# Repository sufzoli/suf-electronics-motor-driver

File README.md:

# suf-electronics-motor-driver
Spindle motor driver for my Chinese CNC router

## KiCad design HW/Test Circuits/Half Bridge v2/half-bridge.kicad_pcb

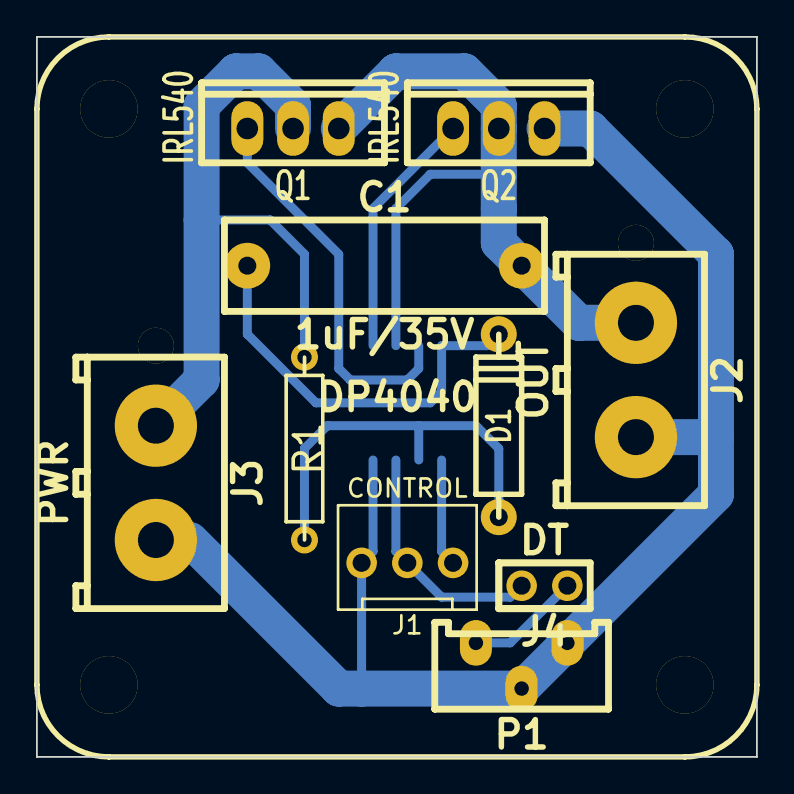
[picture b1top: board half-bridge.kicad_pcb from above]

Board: 2 copper layers, 40.0 x 40.0 mm, 12 parts (1 on the bottom side), 10 nets.

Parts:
C1: 1uF/35V; C6_7x2
D1: 1N5819; D4
DP4040: DP4040
J1: CONTROL; CONN_NCW254-03S
J2: OUT; MOLEX_36538_2
J3: PWR; MOLEX_36538_2
J4: DT; HDR-2
P1: 100K; RV_BOU3296Y
Q1, Q2: IRL540; TO-220_V
R1: 1K8; R4
U1: L6384E; SOIC-8

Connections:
GND: J1.3, J2.2, J3.2, P1.1, P1.2, Q2.3, U1.4
unnamed: J1.1, U1.1
unnamed: J1.2, J4.2, U1.3
unnamed: J4.1, P1.3
unnamed: Q1.1, U1.7
unnamed: Q2.1, U1.5
unnamed: C1.1, D1.2, U1.8
unnamed: D1.1, R1.1, U1.2
unnamed: C1.2, J2.1, Q1.3, Q2.2, U1.6
VCC: J3.1, Q1.2, R1.2

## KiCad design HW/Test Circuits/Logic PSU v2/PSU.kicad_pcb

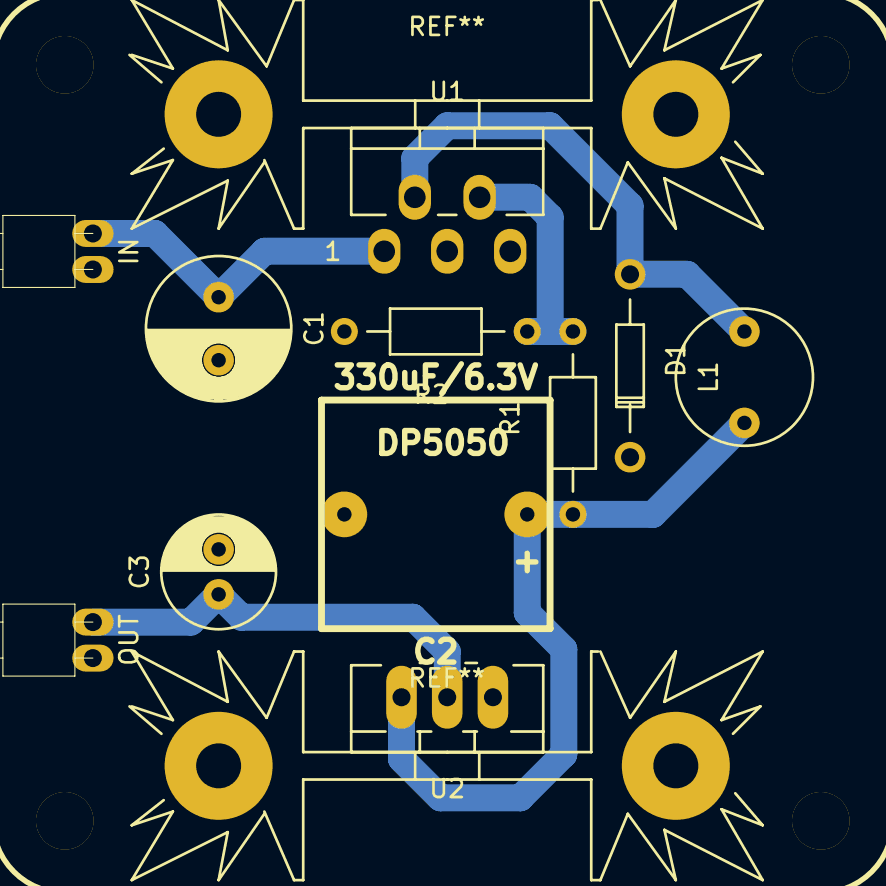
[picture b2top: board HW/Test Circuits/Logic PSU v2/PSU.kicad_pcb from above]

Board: 2 copper layers, 12 parts (0 on the bottom side), 6 nets.

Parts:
C1: 100uF/63V; C_Radial_D8_L11.5_P3.5
C2: 330uF/6.3V; C4P_5X5
C3: 10uF/6,3V; C_Radial_D6.3_L11.2_P2.5
D1: 1N5819; Diode_DO-35_SOD27_Horizontal_RM10
DP5050: DP5050
J1: IN; CONN_NCW254-02R
J2: OUT; CONN_NCW254-02R
L1: 330uH; INDUCTOR_V
R1: 10K; Resistor_Horizontal_RM10mm
R2: 3,3K; Resistor_Horizontal_RM10mm
U1: LM2575; Pentawatt_Neutral_Staggered_Verical_TO220-5-T05D
U2: LD1117V33; TO-220_Neutral123_Vertical_LargePads

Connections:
GND: C1.2, C2.2, C3.2, D1.1, J1.1, J2.1, R2.2, U1.3, U1.5, U2.1
unnamed: C1.1, J1.2, U1.1
unnamed: C2.1, L1.2, R1.1, U2.3
unnamed: C3.1, J2.2, U2.2
unnamed: D1.2, L1.1, U1.2
unnamed: R1.2, R2.1, U1.4

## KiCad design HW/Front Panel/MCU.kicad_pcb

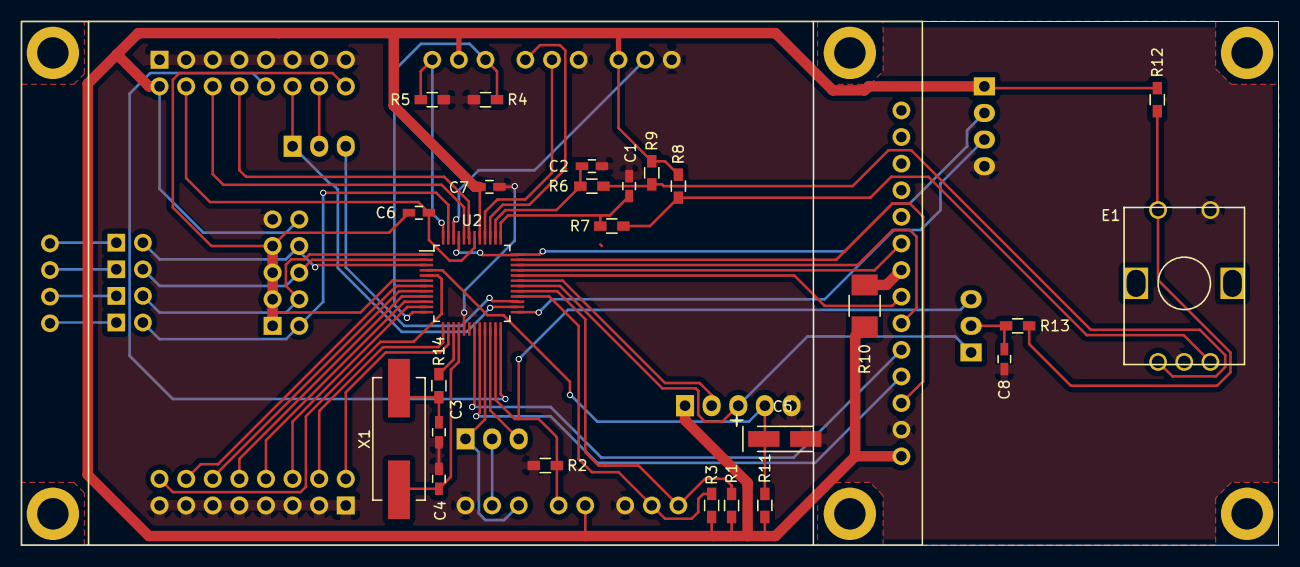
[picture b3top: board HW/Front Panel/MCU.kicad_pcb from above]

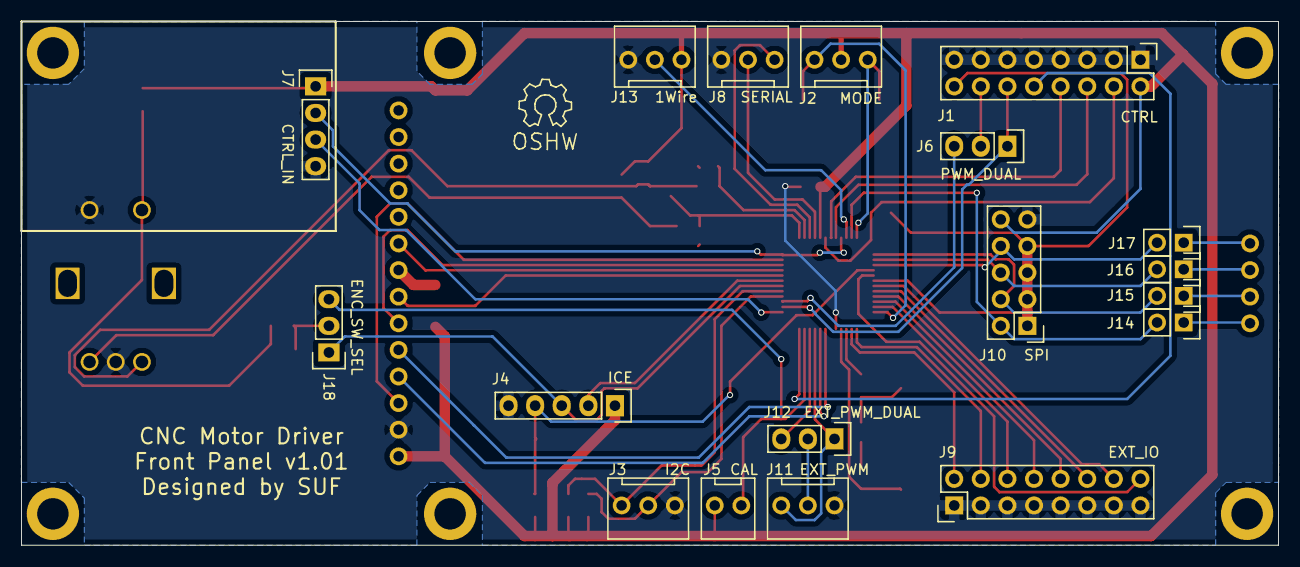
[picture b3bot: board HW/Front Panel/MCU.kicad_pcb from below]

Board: 2 copper layers, 120.0 x 50.0 mm, 46 parts (18 on the bottom side), 58 nets.

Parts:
C1, C2, C8: 10nF; C_0603_HandSoldering
C3, C4: 22pF; C_0603_HandSoldering
C5: 10uF/10V Tantalum; TantalC_SizeA_EIA-3216_HandSoldering
C6, C7: 100nF; C_0603_HandSoldering
E1: EC11P20
J1: CTRL; Pin_Header_Straight_2x08
J2: MODE; CONN_NCW254-03S
J3: I2C; CONN_NCW254-03S
J4: ICE; Pin_Header_Straight_1x05
J5: CAL; CONN_NCW254-02S
J6: PWM_DUAL; Pin_Header_Straight_1x03
J7: CTRL_IN; Pin_Header_Straight_1x04
J8: SERIAL; CONN_NCW254-03S
J9: EXT_IO; Pin_Header_Straight_2x08
J10: SPI; Pin_Header_Straight_2x05
J11: EXT_PWM; CONN_NCW254-03S
J12: EXT_PWM_DUAL; Pin_Header_Straight_1x03
J13: 1Wire; CONN_NCW254-03S
J14, J15, J16, J17: JUMPER; Pin_Header_Straight_1x02
J18: ENC_SW_SEL; Pin_Header_Straight_1x03
MNT_HOLE_3, MNT_HOLE_3#2: Val**; MNT_HOLE_3
R1, R3, R6, R7, R8, R9, R11, R12, R13: 10K; R_0603_HandSoldering
R2, R4, R5: 47K; R_0603_HandSoldering
R10: 3R9; R_1210_HandSoldering
R14: 33; R_0603_HandSoldering
U2: M0516LDN; LQFP-48_7x7mm_Pitch0.5mm
U3: TJCTM24028-SPI
X1: XTAL; Crystal_HC49-SD_SMD

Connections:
1Wire: J13.2, U2.46
ADC_I: J1.8, U2.43
ADC_U: J1.6, U2.44
CAL: J5.2, J18.3, R2.1, U2.23
ENC_A: C2.1, R6.1, U2.38
ENC_B: C1.1, R7.1, U2.37
GND: C1.2, C2.2, C3.1, C4.1, C5.2, C7.2, C8.2, E1.1, E1.5, J1.1, J1.3, J1.5, J1.7, J1.9, J1.11, J1.13, J1.15, J3.3, J4.5, J7.4, J8.3, J9.1, J9.3, J9.5, J9.7, J9.9, J9.11, J9.13, J9.15, J10.9, J11.3, J13.3, R2.2, R4.2, R5.2, U2.17, U3.2
GNDA: C6.2, J1.16, J10.1, J10.3, J10.5, J10.7, U2.6
I2C_SCL: J3.2, R3.2, U2.28
I2C_SDA: J3.1, R1.2, U2.29
MODE_AUTO: J2.3, R4.1, U2.12
MODE_RPM: J2.1, R5.1, U2.48
unnamed: C3.2, R14.1, X1.2
unnamed: C8.1, J18.2, R13.2
unnamed: E1.2, R6.2, R9.2
unnamed: E1.3, R7.2, R8.2
unnamed: E1.4, R12.2, R13.1
unnamed: J1.14, J6.2
unnamed: J11.2, J12.2
unnamed: J14.1, U3.15
unnamed: J15.1, U3.16
unnamed: J16.1, U3.17
unnamed: J17.1, U3.18
unnamed: R10.2, U3.8
PP0: J9.16, U2.5
PP1: J9.14, U2.7
PP2: J9.12, U2.8
PP3: J9.10, U2.9
PP4: J9.8, U2.10
PP5: J9.6, U2.11
PP6: J9.4, U2.13
PP7: J9.2, U2.14
PWM_0: J1.12, J6.1, U2.26
PWM_1: J6.3, U2.27
PWM_2: J11.1, J12.1, U2.21
PWM_3: J12.3, U2.22
RPM_IN: J1.10, U2.24
RXD: J8.1, U2.39
SPINDLE_SPEED: J7.2, U2.36, U2.45
SPINDLE_SWITCH: J7.3, U2.25
SPI_MISO: J10.6, J16.2, U2.2
SPI_MOSI: J10.4, J15.2, U2.1
SPI_SCK: J10.8, J17.2, U2.3
SPI_SS: J10.2, J14.2, U2.47
TFT_CS: U2.35, U3.3
TFT_DC: U2.19, U3.5
TFT_MISO: U2.33, U3.9
TFT_MOSI: U2.34, U3.6
TFT_RST: U2.20, U3.4
TFT_SCK: U2.32, U3.7
TICECLK: J4.3, J18.1, U2.30
TICEDAT: J4.2, U2.31
TICERST: C5.1, J4.4, R11.2, U2.4
TXD: J8.2, U2.40
VCC: C7.1, J1.2, J2.2, J4.1, J5.1, J7.1, J10.10, J13.1, R1.1, R3.1, R8.1, R9.1, R10.1, R11.1, R12.1, U2.41, U3.1
VDD: C6.1, J1.4, U2.42
X1: C4.2, U2.16, X1.1
X2: R14.2, U2.15

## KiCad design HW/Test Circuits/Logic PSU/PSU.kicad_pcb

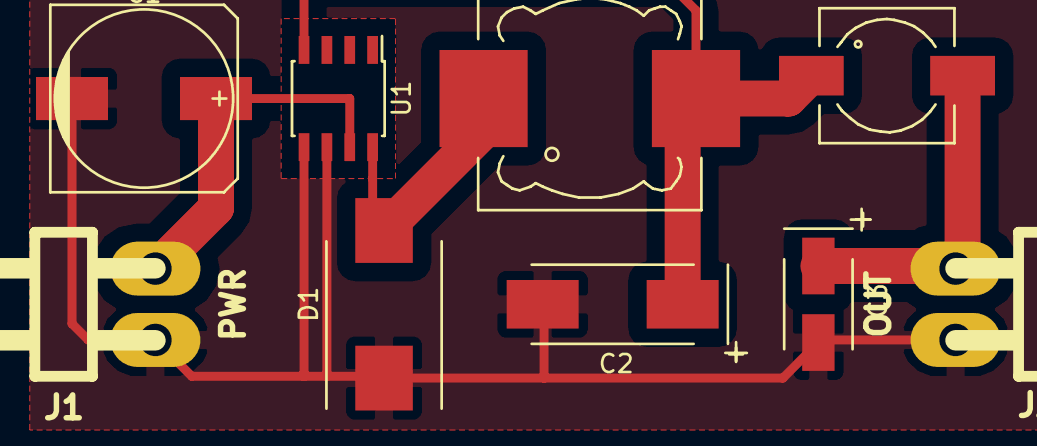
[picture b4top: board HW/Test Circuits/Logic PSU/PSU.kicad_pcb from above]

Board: 2 copper layers, 9 parts (0 on the bottom side), 5 nets.

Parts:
C1: 100uF/63V; c_elec_10x10.5
C2: 220uF/10V Tantalum; TantalC_SizeD_EIA-7343_HandSoldering
C3: 100uF/6.3V Tantalum; TantalC_SizeB_EIA-3528_HandSoldering
D1: SS14; Diode-DO-214AB_Handsoldering
J1: PWR; CONN_NCW396-02R
J2: OUT; CONN_NCW396-02R
L1: 100uH; Choke_SMD_Wuerth-WE-PD-Typ-LS_Handsoldering
L2: 3.3uH; Choke_SMD_Wuerth-WE-PD-Typ-M-Typ-S_Handsoldering
U1: LM2594HVM-3.3; SOIC-8_3.9x4.9mm_Pitch1.27mm

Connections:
GND: C1.2, C2.2, C3.2, D1.1, J1.1, J2.2, U1.5, U1.6
unnamed: C2.1, L1.2, L2.1, U1.4
unnamed: D1.2, L1.1, U1.8
VCC: C3.1, J2.1, L2.2
VDD: C1.1, J1.2, U1.7

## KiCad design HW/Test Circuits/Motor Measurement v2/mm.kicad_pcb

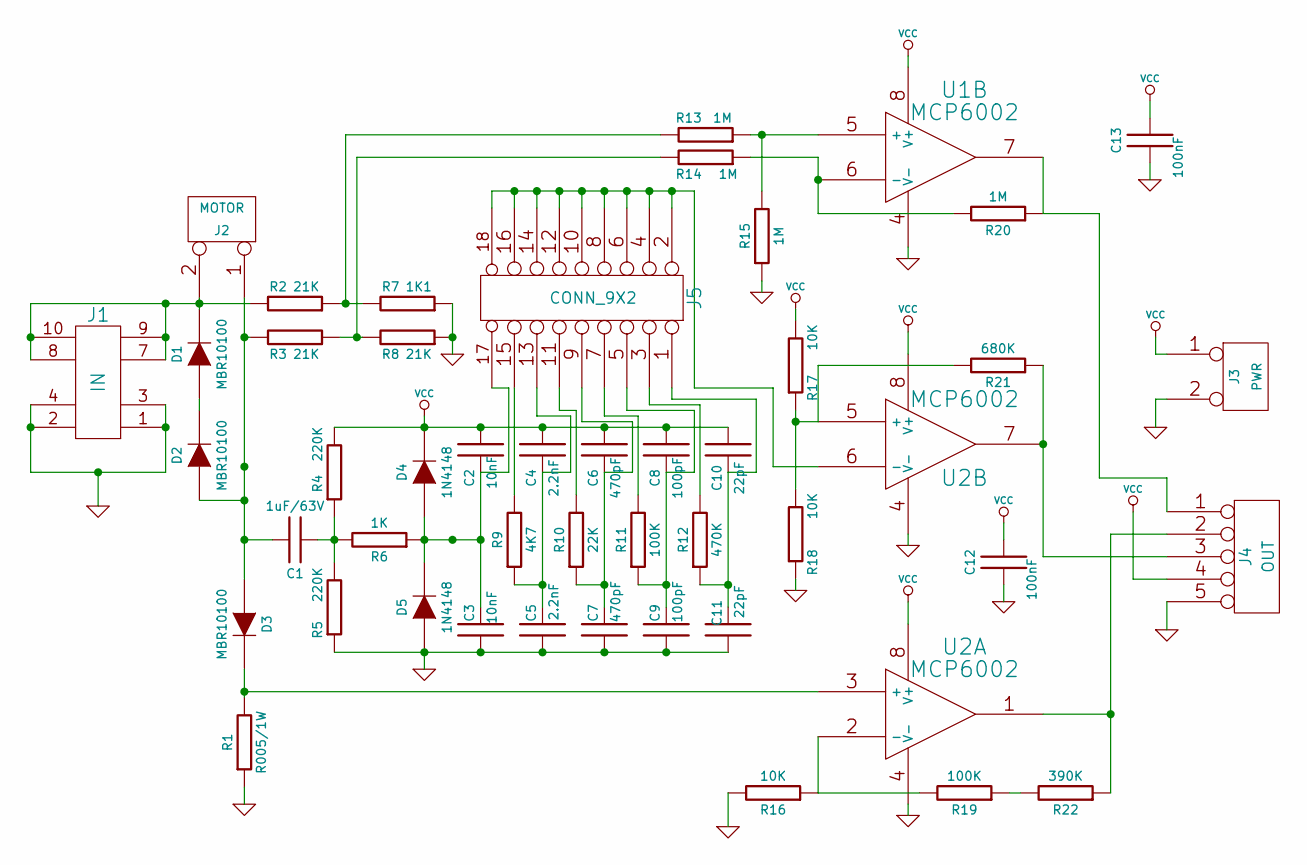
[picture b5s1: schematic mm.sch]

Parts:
C1: 1uF/63V; C2_3x1,75
C2, C3: 10nF; C1
C4, C5: 2.2nF; C1
C6, C7: 470pF; C1
C8, C9: 100pF; C1
C10, C11: 22pF; C1
C12, C13: 100nF; C1
D1, D2, D3: MBR10100; TO220-2
D4, D5: 1N4148; D2
J1: IN; MD-TEST-HDR-F
J2: MOTOR; MOLEX_36538_2
J3: PWR; CONN_NCW254-02S
J4: OUT; CONN_NCW254-05S
J5: CONN_9X2; HDR-9x2
R1: R005/1W; SM2512
R2, R3, R8: 21K; R4
R4, R5: 220K; R4
R6: 1K; R4
R7: 1K1; R4
R9: 4K7; R4
R10: 22K; R4
R11, R19: 100K; R4
R12: 470K; R4
R13, R14, R15, R20: 1M; R4
R16, R17, R18: 10K; R4
R21: 680K; R4
R22: 390K; R4
U1, U2: MCP6002; DIP-8

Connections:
GND: C3.2, C5.2, C7.2, C9.2, C11.2, C12.2, C13.2, D5.1 (A), J1.1, J1.2, J1.3, J1.4, J3.2 (PM), J4.5, R1.2, R5.2, R7.2, R8.2, R15.2, R16.1, R18.2, U1.4 (V-), U2.4 (V-)
unnamed: C1.1, D2.3 (A), D3.3 (A), J2.1, R3.1
unnamed: C1.2, R4.2, R5.1, R6.1
unnamed: C2.2, C3.1, D4.1 (A), D5.2 (K), J5.17, R6.2
unnamed: C4.2, C5.1, J5.13, R9.2
unnamed: C6.2, C7.1, J5.9, R10.2
unnamed: C8.2, C9.1, J5.5, R11.2
unnamed: C10.2, C11.1, J5.1, R12.2
unnamed: D1.1 (K), J1.7, J1.8, J1.9, J1.10, J2.2 (PM), R2.1
unnamed: D1.3 (A), D2.1 (K)
unnamed: D3.1 (K), R1.1, U2.3 (+)
unnamed: J4.1, R20.2, U1.7
unnamed: J4.2, R22.2, U2.1
unnamed: J4.3, R21.2, U2.7
unnamed: J5.3, R12.1
unnamed: J5.7, R11.1
unnamed: J5.2, J5.4, J5.6, J5.8, J5.10, J5.12, J5.14, J5.16, J5.18, U2.6 (-)
unnamed: J5.11, R10.1
unnamed: J5.15, R9.1
unnamed: R2.2, R7.1, R13.1
unnamed: R13.2, R15.1, U1.5 (+)
unnamed: R3.2, R8.1, R14.1
unnamed: R14.2, R20.1, U1.6 (-)
unnamed: R16.2, R19.1, U2.2 (-)
unnamed: R17.2, R18.1, R21.1, U2.5 (+)
unnamed: R19.2, R22.1
VCC: C2.1, C4.1, C6.1, C8.1, C10.1, C12.1, C13.1, D4.2 (K), J3.1, J4.4, R4.1, R17.1, U1.8 (V+), U2.8 (V+)

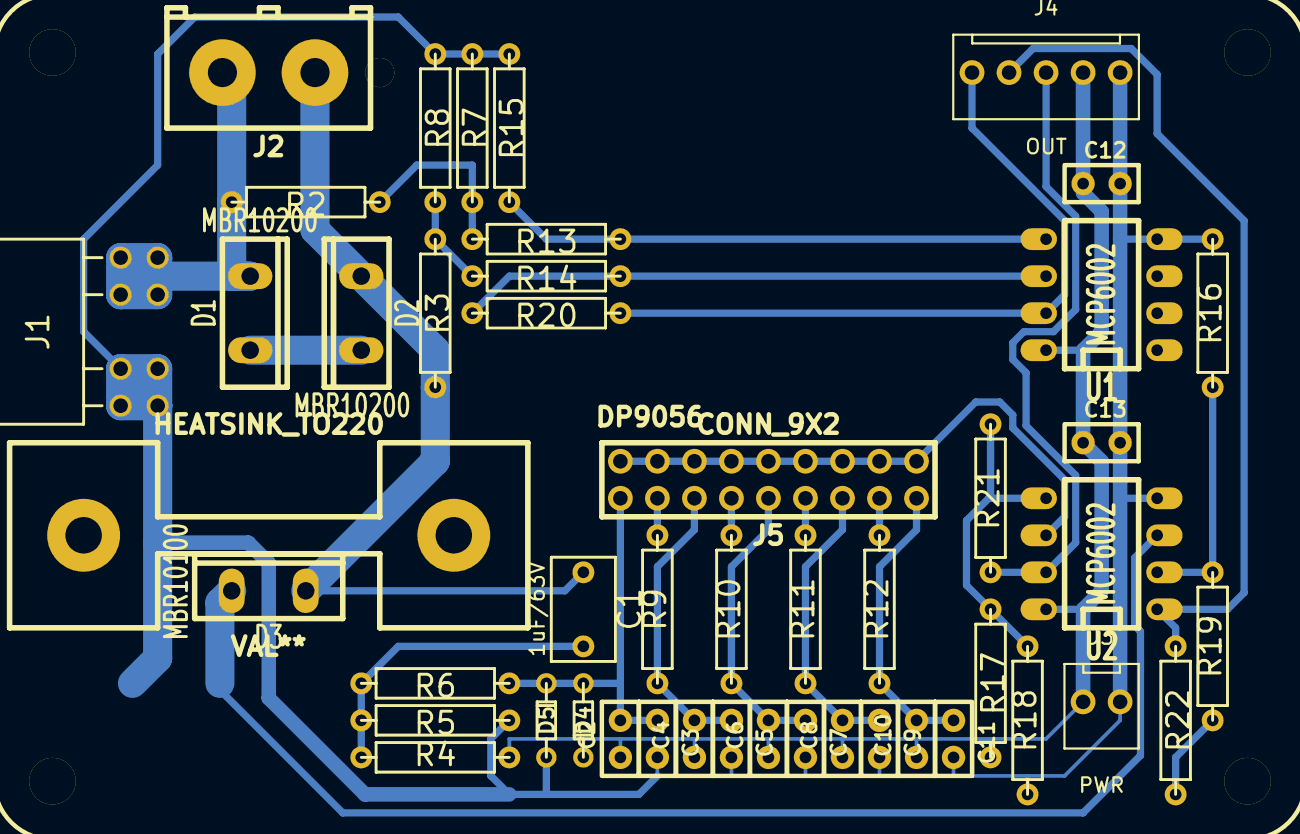
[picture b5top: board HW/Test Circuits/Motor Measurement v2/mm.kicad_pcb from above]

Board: 2 copper layers, 49 parts (1 on the bottom side), 27 nets.

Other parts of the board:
DP9056: DP9056
HEATSINK_TO220: VAL**; HEATSINK_TO220

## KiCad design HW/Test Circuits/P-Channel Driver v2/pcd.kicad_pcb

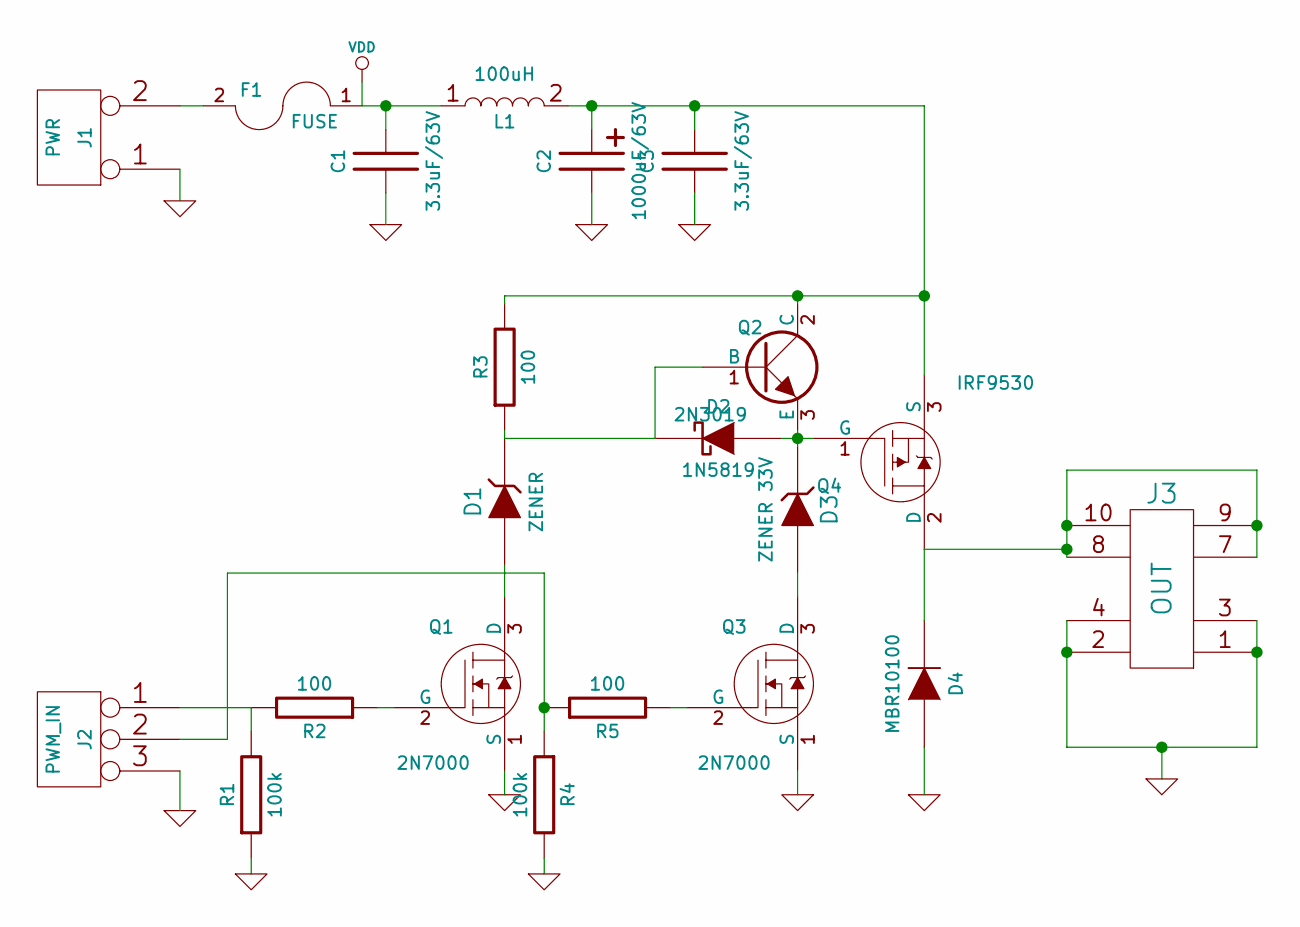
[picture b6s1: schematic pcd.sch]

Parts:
C1, C3: 3.3uF/63V; C2_3x3
C2: 1000uF/63V; C3P_D7
D1: ZENER; D3
D2: 1N5819; D3
D3: ZENER 33V; D3
D4: MBR10100; TO220-2
F1: FUSE; AUTOFUSE
J1: PWR; MOLEX_36538_2
J2: PWM_IN; CONN_NCW254-03S
J3: OUT; MD-TEST-HDR-M
L1: 100uH; L-TOROID-D35X5
Q1, Q3: 2N7000; TO-92_V
Q2: 2N3019; TO-39
Q4: IRF9530; TO-220_V
R1, R4: 100k; R4
R2, R3, R5: 100; R4

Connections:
GND: C1.2, C2.2, C3.2, D4.3 (A), J1.1, J2.3, J3.1, J3.2, J3.3, J3.4, Q1.1 (S), Q3.1 (S), R1.2, R4.1
unnamed: F1.2, J1.2 (PM)
unnamed: C2.1, C3.1, L1.2, Q2.2 (C), Q4.3 (S), R3.1
unnamed: D2.1 (A), D3.2 (K), Q2.3 (E), Q4.1 (G)
unnamed: Q1.2 (G), R2.2
unnamed: Q3.2 (G), R5.1
unnamed: J2.1, R1.1, R2.1
unnamed: D1.1 (A), Q1.3 (D)
unnamed: D1.2 (K), D2.2 (K), Q2.1 (B), R3.2
unnamed: D4.1 (K), J3.7, J3.8, J3.9, J3.10, Q4.2 (D)
unnamed: J2.2 (PM), R4.2, R5.2
unnamed: D3.1 (A), Q3.3 (D)
VDD: C1.1, F1.1, L1.1

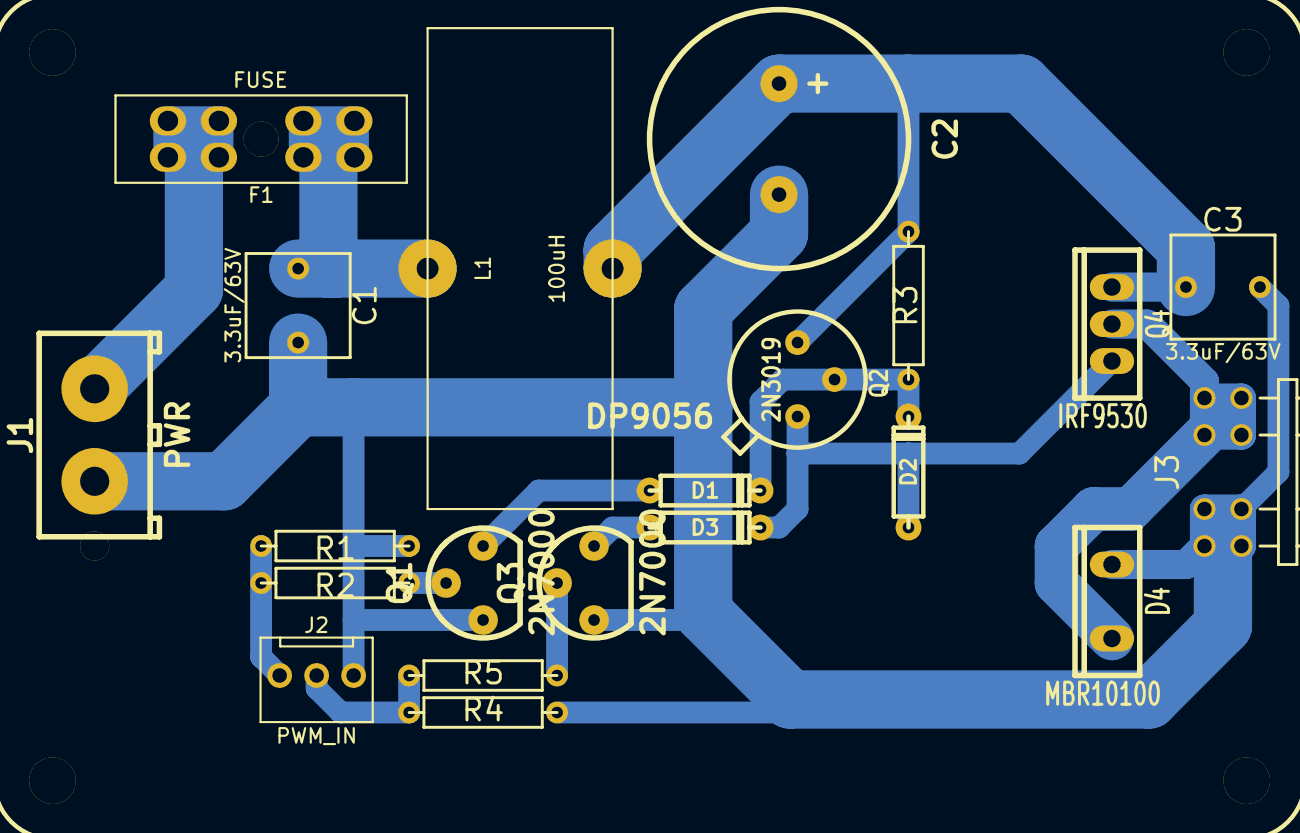
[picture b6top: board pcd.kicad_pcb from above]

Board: 2 copper layers, 22 parts (0 on the bottom side), 13 nets.

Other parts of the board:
DP9056: DP9056

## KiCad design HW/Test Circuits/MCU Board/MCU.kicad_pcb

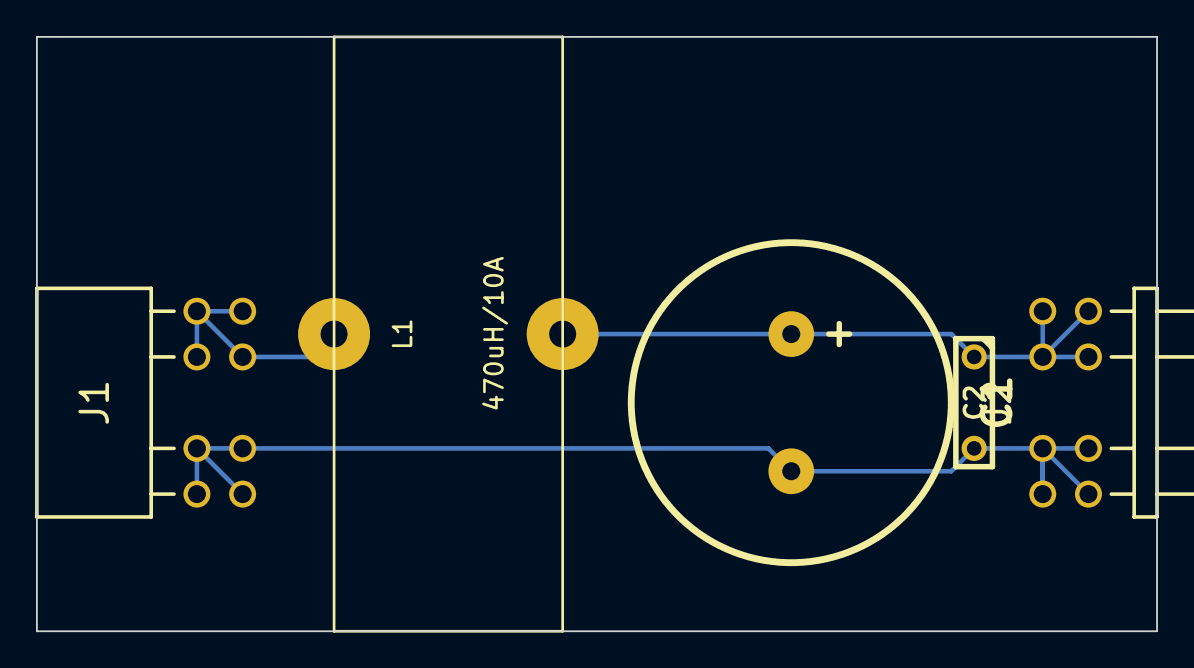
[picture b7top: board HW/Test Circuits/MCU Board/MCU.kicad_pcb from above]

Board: 2 copper layers, 62.2 x 33.0 mm, 5 parts (0 on the bottom side), 3 nets.

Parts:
C1: 1000uF/63V; C3P_D7
C2: 10nF/100V; C2
J1: IN; MD-TEST-HDR-F
J2: OUT; MD-TEST-HDR-M
L1: 470uH/10A; L-TOROID-D35X5

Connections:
GND: C1.2, C2.2, J1.1, J1.2, J1.3, J1.4, J2.1, J2.2, J2.3, J2.4
unnamed: J1.7, J1.8, J1.9, J1.10, L1.1
unnamed: C1.1, C2.1, J2.7, J2.8, J2.9, J2.10, L1.2

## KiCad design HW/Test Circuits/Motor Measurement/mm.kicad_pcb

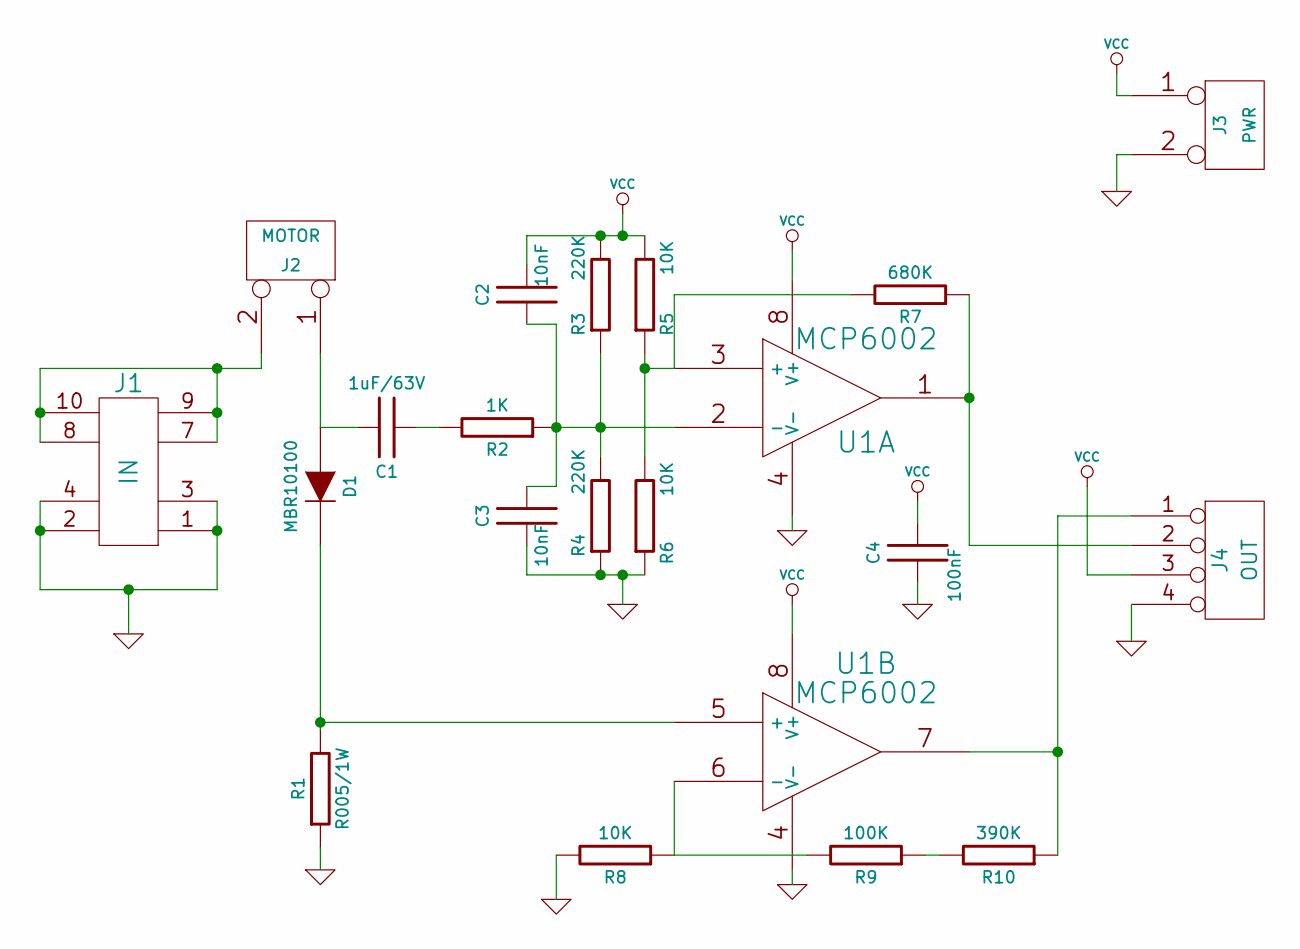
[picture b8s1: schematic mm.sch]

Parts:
C1: 1uF/63V; C2_3x1,75
C2, C3: 10nF; C2
C4: 100nF; C1
D1: MBR10100; TO220-2
J1: IN; MD-TEST-HDR-F
J2: MOTOR; MOLEX_36538_2
J3: PWR; CONN_NCW254-02S
J4: OUT; CONN_NCW254-04S
R1: R005/1W; R4_5_6
R2: 1K; R4
R3, R4: 220K; R4
R5, R6, R8: 10K; R4
R7: 680K; R4
R9: 100K; R4
R10: 390K; R4
U1: MCP6002; DIP-8

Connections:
GND: C3.2, C4.2, J1.1, J1.2, J1.3, J1.4, J3.2 (PM), J4.4, R1.2, R4.2, R6.2, R8.1, U1.4 (V-)
unnamed: C1.2, R2.1
unnamed: J1.7, J1.8, J1.9, J1.10, J2.2 (PM)
unnamed: J4.1, R10.2, U1.7
unnamed: C2.2, C3.1, R2.2, R3.2, R4.1, U1.2 (-)
unnamed: R5.2, R6.1, R7.1, U1.3 (+)
unnamed: C1.1, D1.3 (A), J2.1
unnamed: R9.2, R10.1
unnamed: R8.2, R9.1, U1.6 (-)
unnamed: J4.2, R7.2, U1.1
unnamed: D1.1 (K), R1.1, U1.5 (+)
VCC: C2.1, C4.1, J3.1, J4.3, R3.1, R5.1, U1.8 (V+)

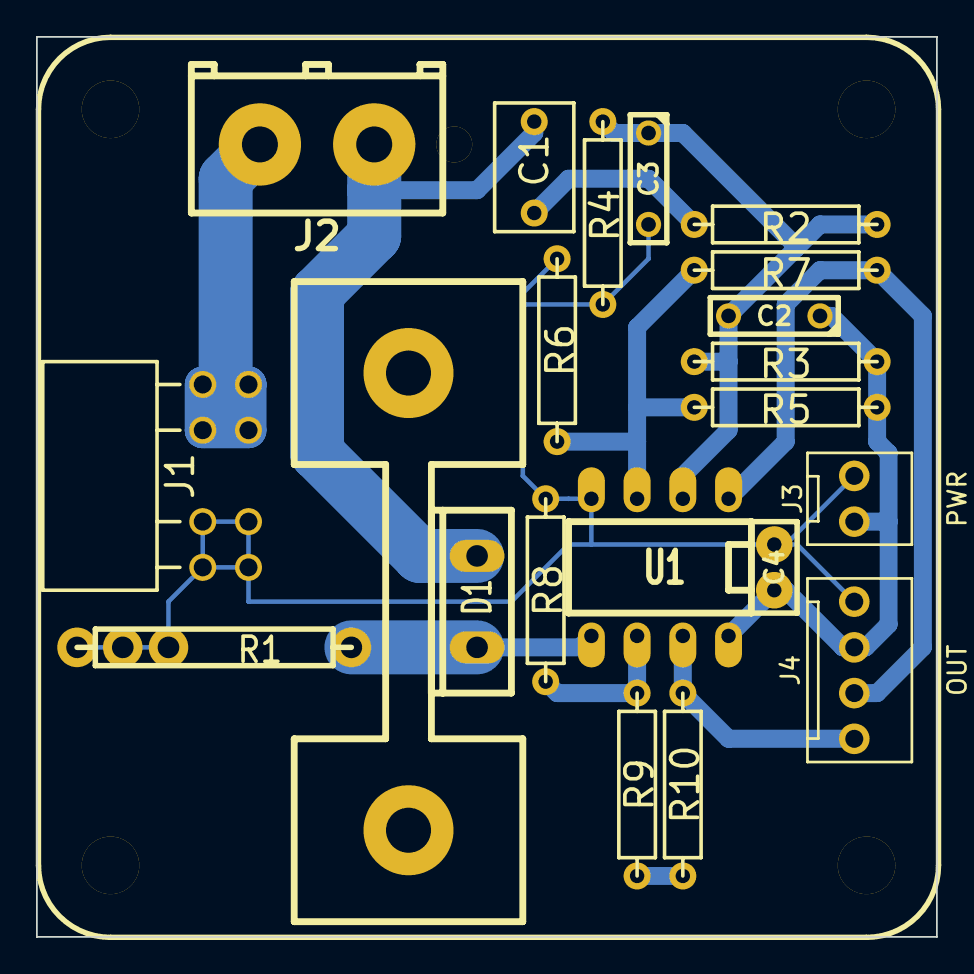
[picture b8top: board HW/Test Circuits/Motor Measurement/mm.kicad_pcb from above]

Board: 2 copper layers, 50.0 x 50.0 mm, 22 parts (0 on the bottom side), 12 nets.

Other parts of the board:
DP5050: DP5050
HEATSINK_TO220: VAL**; HEATSINK_TO220

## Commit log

2015-01-23 Symulation added
2015-01-24 Schematic changed
2015-01-26 Schematic modified
2015-01-26 Schematic modified - changed to MCP6002
2015-01-29 Schematic revert
2015-02-09 Schematic change
2015-02-09 Restructuring hardware
2015-02-10 Motor Measurement circuit added (not complete)
2015-02-12 Motor Measurement Circuit added
2015-02-12 P-Channel driver schematic added
2015-02-14 The first wave of test boards finished
2015-02-20 Motor speed sensor filter simulation added
2015-02-20 Full driver circuit added (unfinished)
2015-02-21 Driver schematic (unfinished)
2015-02-27 Passive filter simulation added
2015-02-27 MCU Test board added High order passive filter simulation added LCD Display test code added
2015-03-05 Driver firmware sources added (not complette)
2015-03-05 File cleanup and reorganization
2015-03-06 PWM Controller with rotary encoder works? The rotary encoder handling buggy, the PWM change not tested
2015-03-08 RPM Measurement added (multiply be 12 missing) Known errors: - display initialization To do: - timed, queued display handling - code reorganization
2015-03-12 Stable LCD driver and test added (functions missing)
2015-03-12 LCD Code completed (no queue handling, testing needed)
2015-03-13 LCD SW changed, comutator handling added Test signal added
2015-03-16 RPM counter finished (I hope)
2015-03-17 RPM-Duty Cycle conversion calibration added (unfinished)
2015-03-17 LCD Number handling added
2015-03-20 EXPWM, PID added - preliminary
2015-03-20 Ported to EXPWM - preliminary
2015-03-23 ili9341 driver added - preliminary
2015-03-23 ILI9341 font handling added - preliminary
2015-03-26 ILI9341 - Character displaying changed (still unfinished)
2015-03-26 RPM display switched to the TFT (not tested)
2015-03-27 ILI9341 - Number display fixed Init modularization
2015-03-30 Calibration, Control for calibration, calibration uart communication, Uart PC software (just test) added.
2015-03-30 Graceful motor stop added
2015-04-01 PID Controller code finished (untested) MODE switching code finished (untested)
2015-04-01 Serial logger added - write data to file (untested)
2015-04-01 Protection diodes added to the schematic, changed to 3.3V
2015-04-03 EXPWM duty read function added Control bugfix PID bugfix
2015-04-05 Continous serial logging added multiple header declaration fixed
2015-04-06 Test code added for half wave measurement error
2015-04-06 Test code added for half wave measurement error (corrected)
2015-04-06 Test code added for half wave measurement error 2nd try
2015-04-06 Enable de-bounce for the timer capture pin.
2015-04-21 Updated MOSFET driver circuit/simulation added
2015-04-25 Motor Measurement V2 added
2015-04-25 MCU Board - start
2015-06-19 Logic PSU Test board updated +cleaning
2015-06-19 MCU Board renamed to MCU Breakout Cleanup, no board layout yet
2015-06-19 MCU Board v1 updated +cleanup DO NOT BUILD IT, BUGGY !!!
2015-06-19 MCU Board v2 added - unfinished
2015-06-19 Motor Measurement v2 cleanup
2015-06-19 Hardware reorganization + cleanup MCUv2 renamed to Front Panel
2015-06-19 Front Panel MCU pins reorganized
2015-06-22 Pictures/drawing of the JP-3163B board
2015-07-03 Before Front Panel next revision
2015-07-03 Front Panel schematic 1.01 added
2015-07-03 Front Panel PCB added. Unfinished - just for transfer
2015-07-06 Front Panel Schematic v1.01 + PCB design added
2015-08-19 Front Panel SW added - WIP
2015-09-30 RPM Count Refactor Logic PSU v2 added
2016-02-24 Cleanup
2021-03-20 Add test circuit
